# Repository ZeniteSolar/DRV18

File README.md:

# DRV18
Half-Bridge Mosfet Driver

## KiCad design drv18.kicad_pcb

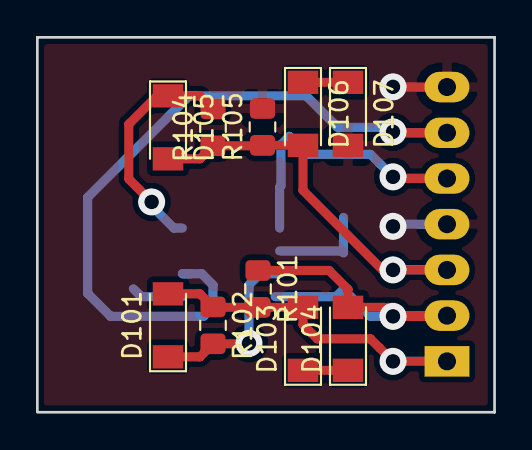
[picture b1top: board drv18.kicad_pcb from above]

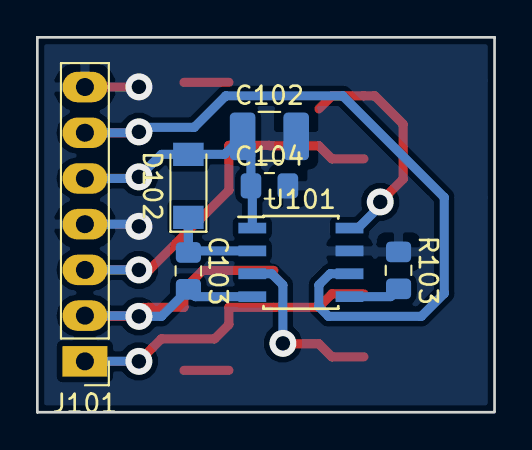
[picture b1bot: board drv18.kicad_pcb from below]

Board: 2 copper layers, 25.4 x 20.8 mm, 17 parts (7 on the bottom side), 12 nets.

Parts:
C102: 10u; C_1210_3225Metric_Pad1.42x2.65mm_HandSolder
C103, C104: 100n; C_0805_2012Metric_Pad1.15x1.40mm_HandSolder
D101, D102, D105: LL4148; D_MiniMELF
D103, D104, D106, D107: 15V; D_MiniMELF
J101: Conn_01x07; PinHeader_1x07_P2.54mm_Vertical
R101, R105: 10k; R_0805_2012Metric_Pad1.15x1.40mm_HandSolder
R102, R104: 1R; R_0805_2012Metric_Pad1.15x1.40mm_HandSolder
R103: 100k; R_0805_2012Metric_Pad1.15x1.40mm_HandSolder
U101: LM5104; SOIC-8_3.9x4.9mm_P1.27mm

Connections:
+12V: C102.1, C104.1, D102.2, J101.5, U101.1
/HG: D101.2, D103.2, J101.1, R101.2, R102.1
/HS: C103.2, D104.2, J101.2, R101.1, U101.4
/LG: D105.2, D106.2, J101.3, R104.1, R105.1
/PWM_IN: J101.6, U101.6
GND: C102.2, C104.2, D107.2, J101.4, J101.7, R103.1, R105.2, U101.7
unnamed: C103.1, D102.1, U101.2
unnamed: D101.1, R102.2, U101.3
unnamed: D103.1, D104.1
unnamed: D105.1, R104.2, U101.8
unnamed: D106.1, D107.1
unnamed: R103.2, U101.5

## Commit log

2018-08-22 First version done.
